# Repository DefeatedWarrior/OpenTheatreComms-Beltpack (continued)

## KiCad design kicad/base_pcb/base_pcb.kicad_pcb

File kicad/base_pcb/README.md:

# Base station carrier PCB, rev 0.1

The OpenTheatreComms base station: a carrier for the Waveshare ESP32-P4-NANO with the beltpack's LR2021 radio, a DC input,
and the front-panel controls. It has no audio of its own: the operator's headset is a beltpack plugged into the NANO's
USB-C (or USB-A) port, which the base runs as its local station. The NANO brings Ethernet (for AES67), USB and an optional PoE
module; the carrier brings everything else.

| | |
|---|---|
| Size | 150 x 90 mm, 1.6 mm FR4, 4 layers, four M3 corner holes |
| Stack | F parts + signals + GND pour, In1 solid GND (under the RF lines), In2 signals + 3.3 V pour, B signals + GND pour |
| Parts | All on the top side (JLC Economic assembly, top). Hand-fit: NANO sockets, DC jack, SMAs, LR2021, keys, dial, OLED socket, wire pads |
| DRC | 0 errors, 0 unconnected. 32 warnings, all cosmetic: silkscreen clipped by pad openings, a few overlapping labels, and three library-mismatch notes for the edited footprints |

## What plugs in where

| Rear edge (left to right) | Front area (left to right) |
|---|---|
| NANO: RJ45 (PoE with Waveshare's module) and USB-A | OLED module (1.3 in, 128x64, I2C SH1106) on a 4-pin socket |
| DC jack, 7-24 V, 5.5 x 2.1 mm, centre + | Menu and Back keys, menu dial (EC11 with push) |
| | Four talk keys (12 mm), each with an RGB channel light |
| SMA antenna B, SMA antenna A (915 MHz), Molex 73251-2120 edge jacks | Row of eight RGB beltpack lights |

The NANO's USB-C points toward the front, under the case lid. It's both the flashing port and where the operator's
beltpack plugs in, so the case needs an opening there (or a short USB-C extension to the front panel).

Lights: twelve WS2812B-Mini-V3J (3.5 x 3.5 mm, JLC-assembled) on one 5 V data chain from GPIO32 through the 74AHCT1G125 shifter: channel lights 1-4 first, then pack lights 1-8.

## Power

Any of three sources powers the station, and they can be connected together:

1. **NANO USB-C** (5 V): through the NANO's own reverse-blocking switch.
2. **PoE** (802.3af): Waveshare's PoE module plugs onto the NANO's PoE header and feeds its 5 V rail.
3. **DC jack** (7-24 V): SS34 reverse protection, SMAJ26A clamp, AP63205 5 V 2 A buck, then SS34 D2 onto the NANO's 5 V rail.

The carrier takes its 5 V from that rail (header pins L2, L4, R1) and makes its own 3.3 V with a TLV75733 (radio,
expander, OLED). The NANO's own 3.3 V is left to the NANO.

## NANO pin map

| GPIO | Header pin | Use | GPIO | Header pin | Use |
|---|---|---|---|---|---|
| 7 / 8 | L3 / L5 | I2C SDA / SCL (shared with the NANO's ES8311 at 0x18) | 20 / 21 / 22 / 23 | L13 / L15 / L16 / L7 | LR2021 NSS / SCK / MOSI / MISO |
| 5 | L11 | LR2021 BUSY | 4 | L12 | LR2021 DIO6 (IRQ) |
| 3 | R9 | LR2021 NRESET | 2 | R11 | Antenna switch (high = A) |
| 33 / 46 / 47 / 48 / 6 | L24 / R17 / R15 / R16 / R12 | Free (were the codec's I2S) | 24 / 25 | L18 / L19 | Dial A / B |
| 26 | L21 | Expander interrupt | 32 | L23 | RGB light data (via a 5 V level shifter) |
| 27 | L22 | Spare (test pad TP1) | | | |

Left unconnected because the NANO uses them: GPIO 0/1 (32 kHz crystal option), 37/38 (UART0, the USB-C serial port),
36 (strapping), 45 (SD power), 53 (its speaker amplifier), 54 and the C6 lines (its Wi-Fi chip).

I2C addresses: NANO's ES8311 0x18, TCA9555 expander 0x21, OLED 0x3C.
Expander: P00-P03 talk keys 1-4, P04 Menu, P05 Back, P06 dial push, P07 free, P10 LR2021 DIO5, P11 LR2021 TX/RX enable.

## Radio

Same circuit as the beltpack: LR2021 module, pi match (C12, L2, C13: 0 ohm and two unfitted shunts until tuned), DC block,
PE4259 switch (GPIO2 high = antenna A), DC blocks, two edge SMA jacks. The RF lines are 0.35 mm on the top layer over the
In1 ground (about 50 ohm on JLC's 7628 stack). The 2.4 GHz port has a footprint-only match and U.FL (J4).

Radio capacity, for the firmware: eight beltpack uplinks plus four channel mixes downlink at Opus 24 kbps is about
300 kbps of audio, well inside the LR2021's 915 MHz FLRC rates, so one radio covers 8 packs on 4 channels with TDMA.

## Check before ordering

1. **NANO sockets.** Positions are from Waveshare's own drawing (DXF, 2026-03-31). Plug a NANO into two loose sockets on
   a printout of `fab/base_pcb_front.png` at 1:1, or check a header against the drawing, before ordering.
2. **OLED pin order.** The socket is GND, VCC, SCL, SDA, the most common order for 1.3 in I2C modules, but some modules
   swap GND and VCC. Check yours.
3. **PoE module height.** It sits on top of the NANO, whose board is about 12.6 mm above the carrier (8.5 mm socket,
   2.5 mm header, 1.6 mm board). Measure the module on your NANO before designing the case lid.
4. **Wi-Fi.** The NANO's Wi-Fi antenna (on its C6 module) sits 11 mm above the carrier's ground pour, which detunes it a
   little. The station uses Ethernet, so this only matters if you use Wi-Fi for setup.
5. **RF.** Tune C12, L2, C13 with a VNA, as on the beltpack.

## Rebuilding

Generated from `pcb_base/design.py`: `python3 customlib.py`, `python3 make_sch.py`, `kicad-cli sch export netlist -o
out/base_pcb.net out/base_pcb.kicad_sch`, `python3 chknet.py out/base_pcb.net`, `python3 make_pcb.py`, `python3 finish_pcb.py`,
`python3 dangle.py` (removes the few track stubs the tidy pass leaves), `python3 make_fab.py`.

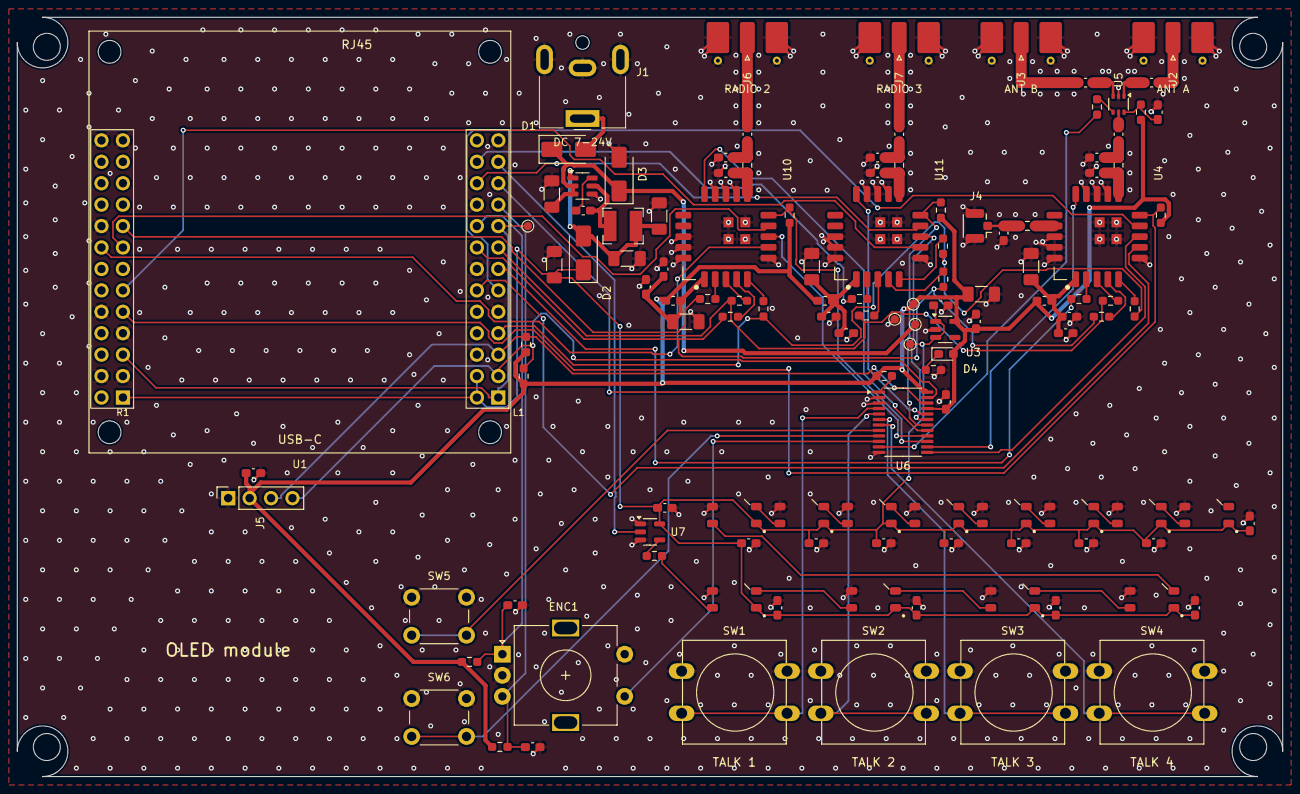
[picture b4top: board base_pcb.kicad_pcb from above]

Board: 2 copper layers, 150.0 x 90.0 mm, 127 parts (0 on the bottom side), 90 nets.

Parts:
C1: 10u; C_1206_3216Metric_Pad1.33x1.80mm_HandSolder
C2, C11, C15, C19, C25, C26, C27, C28, C29, C30, C31, C32, C33, C34, C35, C36, C37, C40, C49: 100n; C_0603_1608Metric_Pad1.08x0.95mm_HandSolder
C3, C4, C5, C8: 22u; C_1206_3216Metric_Pad1.33x1.80mm_HandSolder
C6: 1u; C_0603_1608Metric_Pad1.08x0.95mm_HandSolder
C7, C10, C20, C39, C48: 10u; C_0603_1608Metric_Pad1.08x0.95mm_HandSolder
C9, C38, C47: 47u; C_1206_3216Metric_Pad1.33x1.80mm_HandSolder
C12, C13, C18, C41, C42, C50, C51: DNP; C_0603_1608Metric_Pad1.08x0.95mm_HandSolder
C14, C16, C17, C43, C52: 100p; C_0603_1608Metric_Pad1.08x0.95mm_HandSolder
C21, C22: 10n; C_0603_1608Metric_Pad1.08x0.95mm_HandSolder
D1, D2: SS34; D_SMA
D3: SMAJ26A; D_SMA
D4: green; LED_0603_1608Metric_Pad1.05x0.95mm_HandSolder
ENC1: EC11; RotaryEncoder_Alps_EC11E-Switch_Vertical_H20mm
FB1, FB2, FB3: 0R; L_0603_1608Metric_Pad1.05x0.95mm_HandSolder
H1, H2, H3, H4: M3; MountingHole_3.2mm_M3
J1: DC 7-24 V; BarrelJack_CUI_PJ-063AH_Horizontal
J2: Antenna A; SMA_Molex_73251-2120_EdgeMount_Horizontal
J3: Antenna B; SMA_Molex_73251-2120_EdgeMount_Horizontal
J4: 2.4 GHz; U.FL_Hirose_U.FL-R-SMT-1_Vertical
J5: OLED; PinSocket_1x04_P2.54mm_Vertical
J6: Radio 2 antenna; SMA_Molex_73251-2120_EdgeMount_Horizontal
J7: Radio 3 antenna; SMA_Molex_73251-2120_EdgeMount_Horizontal
L1: 4.7u; L_Bourns-SRN4018
L2, L3, L4, L6: 0; R_0603_1608Metric_Pad0.98x0.95mm_HandSolder
LED1, LED2, LED3, LED4, LED5, LED6, LED7, LED8, LED9, LED10, LED11, LED12: WS2812B-Mini; LED_WS2812B-Mini-V3J_3.5x3.5mm
R1, R2: 4.7k; R_0603_1608Metric_Pad0.98x0.95mm_HandSolder
R3, R9, R10: 1k; R_0603_1608Metric_Pad0.98x0.95mm_HandSolder
R4, R5, R6, R7, R15, R16, R17, R18, R21, R22, R23, R24: 470; R_0603_1608Metric_Pad0.98x0.95mm_HandSolder
R8, R19, R25: 100k; R_0603_1608Metric_Pad0.98x0.95mm_HandSolder
R11, R12, R13: 10k; R_0603_1608Metric_Pad0.98x0.95mm_HandSolder
R14: 33; R_0603_1608Metric_Pad0.98x0.95mm_HandSolder
SW1: Talk 1; SW_PUSH-12mm
SW2: Talk 2; SW_PUSH-12mm
SW3: Talk 3; SW_PUSH-12mm
SW4: Talk 4; SW_PUSH-12mm
SW5: Menu; SW_PUSH_6mm
SW6: Back; SW_PUSH_6mm
TP2: NANO_3V3; TestPoint_Pad_D1.0mm
TP3: VIN; TestPoint_Pad_D1.0mm
TP4: 5V; TestPoint_Pad_D1.0mm
TP5: 3V3; TestPoint_Pad_D1.0mm
TP6: GND; TestPoint_Pad_D1.0mm
U1: ESP32-P4-NANO; ESP32-P4-NANO_Sockets
U2: AP63205WU; TSOT-23-6
U3: TLV75733; SOT-23-5
U4, U10, U11: LR2021; LR2021_Elecrow_10x10mm
U5: PE4259; SOT-363_SC-70-6
U6: TCA9555PWR; TSSOP-24_4.4x7.8mm_P0.65mm
U7: 74AHCT1G125; SOT-23-5

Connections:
+3V3: C7.1, C8.1, C19.1, C20.1, D4.2, FB1.1, FB2.1, FB3.1, J5.2, R1.1, R2.1, R8.1, R10.1, R11.1, R12.1, R13.1, R19.1, R25.1, TP5.1, U3.5, U6.21, U6.24
/+5V: C5.1, C6.1, C25.1, C26.1, C27.1, C28.1, C29.1, C30.1, C31.1, C32.1, C33.1, C34.1, C35.1, C36.1, C37.1, D2.1, LED1.1, LED2.1, LED3.1, LED4.1, LED5.1, LED6.1, LED7.1, LED8.1, LED9.1, LED10.1, LED11.1, LED12.1, TP4.1, U1.L2, U1.L4, U1.R1, U3.1, U3.3, U7.5
/BUCK_BST: C2.1, U2.6
/BUCK_OUT: C3.1, C4.1, D2.2, L1.2, U2.1
/BUCK_SW: C2.2, L1.1, U2.5
/ENC_A: C21.1, ENC1.A, R12.2, U1.L18
/ENC_B: C22.1, ENC1.B, R13.2, U1.L19
/ENC_SW: ENC1.S1, U6.10
/EXP_INT_N: R11.2, U1.L21, U6.1
/I2C_SCL: J5.3, R2.2, U1.L5, U6.22
/I2C_SDA: J5.4, R1.2, U1.L3, U6.23
/KEY1: SW1.2, U6.4
/KEY2: SW2.2, U6.5
/KEY3: SW3.2, U6.6
/KEY4: SW4.2, U6.7
/KEY_BACK: SW6.2, U6.9
/KEY_MENU: SW5.2, U6.8
/LED_D0: R14.1, U7.4
/LED_D1: LED1.4, R14.2
/LED_D2: LED1.2, LED2.4
/LED_D3: LED2.2, LED3.4
/LED_D4: LED3.2, LED4.4
/LED_D5: LED4.2, LED5.4
/LED_D6: LED5.2, LED6.4
/LED_D7: LED6.2, LED7.4
/LED_D8: LED7.2, LED8.4
/LED_D9: LED8.2, LED9.4
/LED_D10: LED9.2, LED10.4
/LED_D11: LED10.2, LED11.4
/LED_D12: LED11.2, LED12.4
/LED_DIN: U1.L23, U7.2
/LR2_BUSY: U1.R15, U10.9
/LR2_DIO5: U6.16, U10.8
/LR2_DIO6: U1.R16, U10.7
/LR2_MISO_M: R18.2, U10.5
/LR2_MOSI_M: R17.2, U10.4
/LR2_NRESET: R19.2, U6.15, U10.10
/LR2_NSS: R15.1, U1.R17
/LR2_NSS_M: R15.2, U10.2
/LR2_SCK_M: R16.2, U10.3
/LR2_TXRX_EN: U6.17, U10.15
/LR2_VDD: C38.1, C39.1, C40.1, FB2.2, U10.1
/LR3_BUSY: U1.L22, U11.9
/LR3_DIO5: U6.19, U11.8
/LR3_DIO6: U1.R11, U11.7
/LR3_MISO_M: R24.2, U11.5
/LR3_MOSI_M: R23.2, U11.4
/LR3_NRESET: R25.2, U6.18, U11.10
/LR3_NSS: R21.1, U1.L24
/LR3_NSS_M: R21.2, U11.2
/LR3_SCK_M: R22.2, U11.3
/LR3_TXRX_EN: U6.20, U11.15
/LR3_VDD: C47.1, C48.1, C49.1, FB3.2, U11.1
/LR_BUSY: U1.L11, U4.9
/LR_DIO5: U4.8, U6.13
/LR_DIO6: U1.L12, U4.7
/LR_MISO: R7.1, R18.1, R24.1, U1.L7
/LR_MISO_M: R7.2, U4.5
/LR_MOSI: R6.1, R17.1, R23.1, U1.L16
/LR_MOSI_M: R6.2, U4.4
/LR_NRESET: R8.2, U1.R9, U4.10
/LR_NSS: R4.1, U1.L13
/LR_NSS_M: R4.2, U4.2
/LR_SCK: R5.1, R16.1, R22.1, U1.L15
/LR_SCK_M: R5.2, U4.3
/LR_TXRX_EN: U4.15, U6.14
/LR_VDD: C9.1, C10.1, C11.1, FB1.2, U4.1
/NANO_3V3: TP2.1, U1.L1, U1.L17, U1.R5
/PWR_LED_K: D4.1, R3.1
/RF2_ANT: C43.2, J6.1
/RF2_LF: C41.1, L4.1, U10.11
/RF2_LF_M: C42.1, C43.1, L4.2
/RF3_ANT: C52.2, J7.1
/RF3_LF: C50.1, L6.1, U11.11
/RF3_LF_M: C51.1, C52.1, L6.2
/RF_ANT_A: C16.2, J2.1
/RF_ANT_B: C17.2, J3.1
/RF_CTRL: R9.1, U6.11
/RF_CTRL_S: R9.2, U5.4
/RF_HF: L3.1, U4.17
/RF_HF_M: C18.1, J4.1, L3.2
/RF_LF: C12.1, L2.1, U4.11
/RF_LF_M: C13.1, C14.1, L2.2
/RF_SW_1: C16.1, U5.1
/RF_SW_2: C17.1, U5.3
/RF_SW_C: C14.2, U5.5
/RF_SW_VDD: C15.1, R10.2, U5.6
/VIN: C1.1, D1.1, D3.1, TP3.1, U2.2, U2.3
/VIN_RAW: D1.2, J1.1
GND: C1.2, C3.2, C4.2, C5.2, C6.2, C7.2, C8.2, C9.2, C10.2, C11.2, C12.2, C13.2, C15.2, C18.2, C19.2, C20.2, C21.2, C22.2, C25.2, C26.2, C27.2, C28.2, C29.2, C30.2, C31.2, C32.2, C33.2, C34.2, C35.2, C36.2, C37.2, C38.2, C39.2, C40.2, C41.2, C42.2, C47.2, C48.2, C49.2, C50.2, C51.2, D3.2, ENC1.C, ENC1.S2, J1.2, J1.MP, J2.2, J3.2, J4.2, J5.1, J6.2, J7.2, LED1.3, LED2.3, LED3.3, LED4.3, LED5.3, LED6.3, LED7.3, LED8.3, LED9.3, LED10.3, LED11.3, LED12.3, R3.2, SW1.1, SW2.1, SW3.1, SW4.1, SW5.1, SW6.1, TP6.1, U1.L6, U1.L9, U1.L14, U1.L20, U1.L25, U1.R3, U1.R4, U1.R7, U1.R10, U1.R18, U1.R25, U1.R26, U2.4, U3.2, U4.6, U4.12, U4.13, U4.14, U4.18, U4.19, U4.20, U5.2, U6.2, U6.3, U6.12, U7.1, U7.3, U10.6, U10.12, U10.13, U10.14, U10.18, U10.19, U10.20, U11.6, U11.12, U11.13, U11.14, U11.18, U11.19, U11.20

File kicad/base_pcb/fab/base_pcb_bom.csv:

Qty,References,Value,Footprint,Part,Side,Notes
1,C1,10u,C_1206_3216Metric_Pad1.33x1.80mm_HandSolder,1206 X7R 50 V,top,
17,C2 C11 C15 C19 C25 C26 C27 C28 C29 C30 C31 C32 C33 C34 C35 C36 C37,100n,C_0603_1608Metric_Pad1.08x0.95mm_HandSolder,0603 X7R,top,
4,C3 C4 C5 C8,22u,C_1206_3216Metric_Pad1.33x1.80mm_HandSolder,1206 X5R 10 V,top,
1,C6,1u,C_0603_1608Metric_Pad1.08x0.95mm_HandSolder,0603 X5R 10 V,top,
3,C7 C10 C20,10u,C_0603_1608Metric_Pad1.08x0.95mm_HandSolder,0603 X5R 10 V,top,
1,C9,47u,C_1206_3216Metric_Pad1.33x1.80mm_HandSolder,1206 X5R 6.3 V,top,Module bulk (guide: 47u + 10u + 100n)
0,C12 C13 C18 C41 C42 C50 C51,DNP DNP,C_0603_1608Metric_Pad1.08x0.95mm_HandSolder,"0603 C0G, tune",top,Not fitted. 
3,C14 C16 C17,100p,C_0603_1608Metric_Pad1.08x0.95mm_HandSolder,0603 C0G 50 V,top,
2,C21 C22,10n,C_0603_1608Metric_Pad1.08x0.95mm_HandSolder,0603 X7R,top,
0,C38 C47,DNP 47u,C_1206_3216Metric_Pad1.33x1.80mm_HandSolder,1206 X5R 6.3 V,top,Not fitted. 
0,C39 C48,DNP 10u,C_0603_1608Metric_Pad1.08x0.95mm_HandSolder,0603 X5R 10 V,top,Not fitted. 
0,C40 C49,DNP 100n,C_0603_1608Metric_Pad1.08x0.95mm_HandSolder,0603 X7R,top,Not fitted. 
0,C43 C52,DNP 100p,C_0603_1608Metric_Pad1.08x0.95mm_HandSolder,0603 C0G 50 V,top,Not fitted. 
2,D1 D2,SS34,D_SMA,SS34 (SMA),top,
1,D3,SMAJ26A,D_SMA,SMAJ26A,top,Input surge clamp
1,D4,green,LED_0603_1608Metric_Pad1.05x0.95mm_HandSolder,Lite-On LTST-C191KGKT,top,Power light
1,ENC1,EC11,RotaryEncoder_Alps_EC11E-Switch_Vertical_H20mm,"EC11 encoder with push switch, 20 mm shaft",top,Menu dial
1,FB1,0R,L_0603_1608Metric_Pad1.05x0.95mm_HandSolder,0603 0R (or Murata BLM18PG121SN1D),top,Radio supply link: the module has its own ferrite
0,FB2 FB3,DNP 0R,L_0603_1608Metric_Pad1.05x0.95mm_HandSolder,0603 0R (or Murata BLM18PG121SN1D),top,Not fitted. 
1,J1,DC 7-24 V,BarrelJack_CUI_PJ-063AH_Horizontal,"CUI PJ-063AH (5.5 x 2.1 mm, centre +)",top,"DC input, 7-24 V, centre positive. Optional: the NANO's USB-C or a PoE module also powers the station"
1,J2,Antenna A,SMA_Molex_73251-2120_EdgeMount_Horizontal,"Molex 73251-2120 SMA edge-mount jack, 1.6 mm board",top,Antenna A (915 MHz whip)
1,J3,Antenna B,SMA_Molex_73251-2120_EdgeMount_Horizontal,"Molex 73251-2120 SMA edge-mount jack, 1.6 mm board",top,Antenna B (915 MHz whip)
0,J4,DNP 2.4 GHz,U.FL_Hirose_U.FL-R-SMT-1_Vertical,Hirose U.FL-R-SMT-1(10),top,Not fitted. 2.4 GHz fallback antenna: footprint only in v1
1,J5,OLED,PinSocket_1x04_P2.54mm_Vertical,"1x4 female socket for a 1.3 in 128x64 I2C OLED module (SH1106, address 0x3C)",top,"OLED module socket: GND, VCC, SCL, SDA (check your module's pin order)"
0,J6,DNP Radio 2 antenna,SMA_Molex_73251-2120_EdgeMount_Horizontal,"Molex 73251-2120 SMA edge-mount jack, 1.6 mm board",top,Not fitted. Radio 2 antenna (915 MHz whip)
0,J7,DNP Radio 3 antenna,SMA_Molex_73251-2120_EdgeMount_Horizontal,"Molex 73251-2120 SMA edge-mount jack, 1.6 mm board",top,Not fitted. Radio 3 antenna (915 MHz whip)
1,L1,4.7u,L_Bourns-SRN4018,"4.7 uH, 2.5 A, 4x4 mm (Bourns SRN4018-4R7M or equal)",top,
1,L2,0,R_0603_1608Metric_Pad0.98x0.95mm_HandSolder,0603 0R or RF inductor,top,Pi match series element: 0R until tuned
0,L3 L4 L6,DNP 0,R_0603_1608Metric_Pad0.98x0.95mm_HandSolder,0603 0R or RF inductor,top,Not fitted. 
12,LED1 LED2 LED3 LED4 LED5 LED6 LED7 LED8 LED9 LED10 LED11 LED12,WS2812B-Mini,LED_WS2812B-Mini-V3J_3.5x3.5mm,Worldsemi WS2812B-Mini-V3J,top,
0,R1 R2,DNP 4.7k,R_0603_1608Metric_Pad0.98x0.95mm_HandSolder,0603 1%,top,Not fitted. 
3,R3 R9 R10,1k,R_0603_1608Metric_Pad0.98x0.95mm_HandSolder,0603 1%,top,
4,R4 R5 R6 R7,470,R_0603_1608Metric_Pad0.98x0.95mm_HandSolder,0603 1%,top,
1,R8,100k,R_0603_1608Metric_Pad0.98x0.95mm_HandSolder,0603 1%,top,
3,R11 R12 R13,10k,R_0603_1608Metric_Pad0.98x0.95mm_HandSolder,0603 1%,top,
1,R14,33,R_0603_1608Metric_Pad0.98x0.95mm_HandSolder,0603 1%,top,LED data series resistor
0,R15 R16 R17 R18 R21 R22 R23 R24,DNP 470,R_0603_1608Metric_Pad0.98x0.95mm_HandSolder,0603 1%,top,Not fitted. 
0,R19 R25,DNP 100k,R_0603_1608Metric_Pad0.98x0.95mm_HandSolder,0603 1%,top,Not fitted. 
1,SW1,Talk 1,SW_PUSH-12mm,12 x 12 mm tactile switch with round cap,top,Talk 1 key (channel 1)
1,SW2,Talk 2,SW_PUSH-12mm,12 x 12 mm tactile switch with round cap,top,Talk 2 key (channel 2)
1,SW3,Talk 3,SW_PUSH-12mm,12 x 12 mm tactile switch with round cap,top,Talk 3 key (channel 3)
1,SW4,Talk 4,SW_PUSH-12mm,12 x 12 mm tactile switch with round cap,top,Talk 4 key (channel 4)
1,SW5,Menu,SW_PUSH_6mm,"6 x 6 mm tactile switch, 13 mm tall",top,Menu key
1,SW6,Back,SW_PUSH_6mm,"6 x 6 mm tactile switch, 13 mm tall",top,Back key
1,U1,ESP32-P4-NANO,ESP32-P4-NANO_Sockets,"Waveshare ESP32-P4-NANO (SKU 29026) on 2x 2x13 2.54 mm female sockets, 8.5 mm",top,"ESP32-P4 board: Ethernet (PoE module option), USB-C, Wi-Fi 6 co-processor. Plugs in RJ45-first toward the rear"
1,U2,AP63205WU,TSOT-23-6,Diodes AP63205WU-7,top,"5 V, 2 A synchronous buck, 3.8-32 V in"
1,U3,TLV75733,SOT-23-5,TI TLV75733PDBVR,top,"3.3 V, 1 A LDO for the radio, codec and expander (separate from the NANO's own 3.3 V)"
1,U4,LR2021,LR2021_Elecrow_10x10mm,Elecrow LR2021 module (LMM16121D),top,915-928 MHz FLRC radio; 2.4 GHz port for fallback
1,U5,PE4259,SOT-363_SC-70-6,pSemi PE4259-63,top,"Antenna diversity switch, RF1 = antenna A when CTRL is high"
1,U6,TCA9555PWR,TSSOP-24_4.4x7.8mm_P0.65mm,TI TCA9555PWR,top,"IO expander at 0x21 (A0 high): keys, encoder push, antenna switch, radios' DIO5, TX/RX enable and radios 2-3 reset"
1,U7,74AHCT1G125,SOT-23-5,74AHCT1G125 (SOT-23-5),top,3.3 V to 5 V level shift for the LED data line
0,U10 U11,DNP LR2021,LR2021_Elecrow_10x10mm,Elecrow LR2021 module (LMM16121D),top,Not fitted.
